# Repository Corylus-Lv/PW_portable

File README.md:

# PremierWave-EN Portable Board

過去に作った基板のEAGLE設計データを公開します。
LANTRONIX社のPremierWave-ENを使った応用基板ですが、リチウムイオン・バッテリーを使った移動機器に応用できるかもしれません。

**特に注意すべき事項：**  
リチウムイオン・バッテリーを使っているので、バッテリー容量に見合った充電電流を設定しないと、バッテリの破裂・炎上などの大きな事故につながる可能性がありますので、十分注意してください（LTC4055のデータシートを熟読する）

CC BY-NC-SA 3.0

**免責事項：**  
このプロジェクトに掲載した情報については「現状のまま」で、明示であるか暗黙であるかを問わず、何らの保証もありません。 
この情報の利用またはその他の扱いに関連した、請求、損害、その他の義務については一切の責任を負うものではありません。

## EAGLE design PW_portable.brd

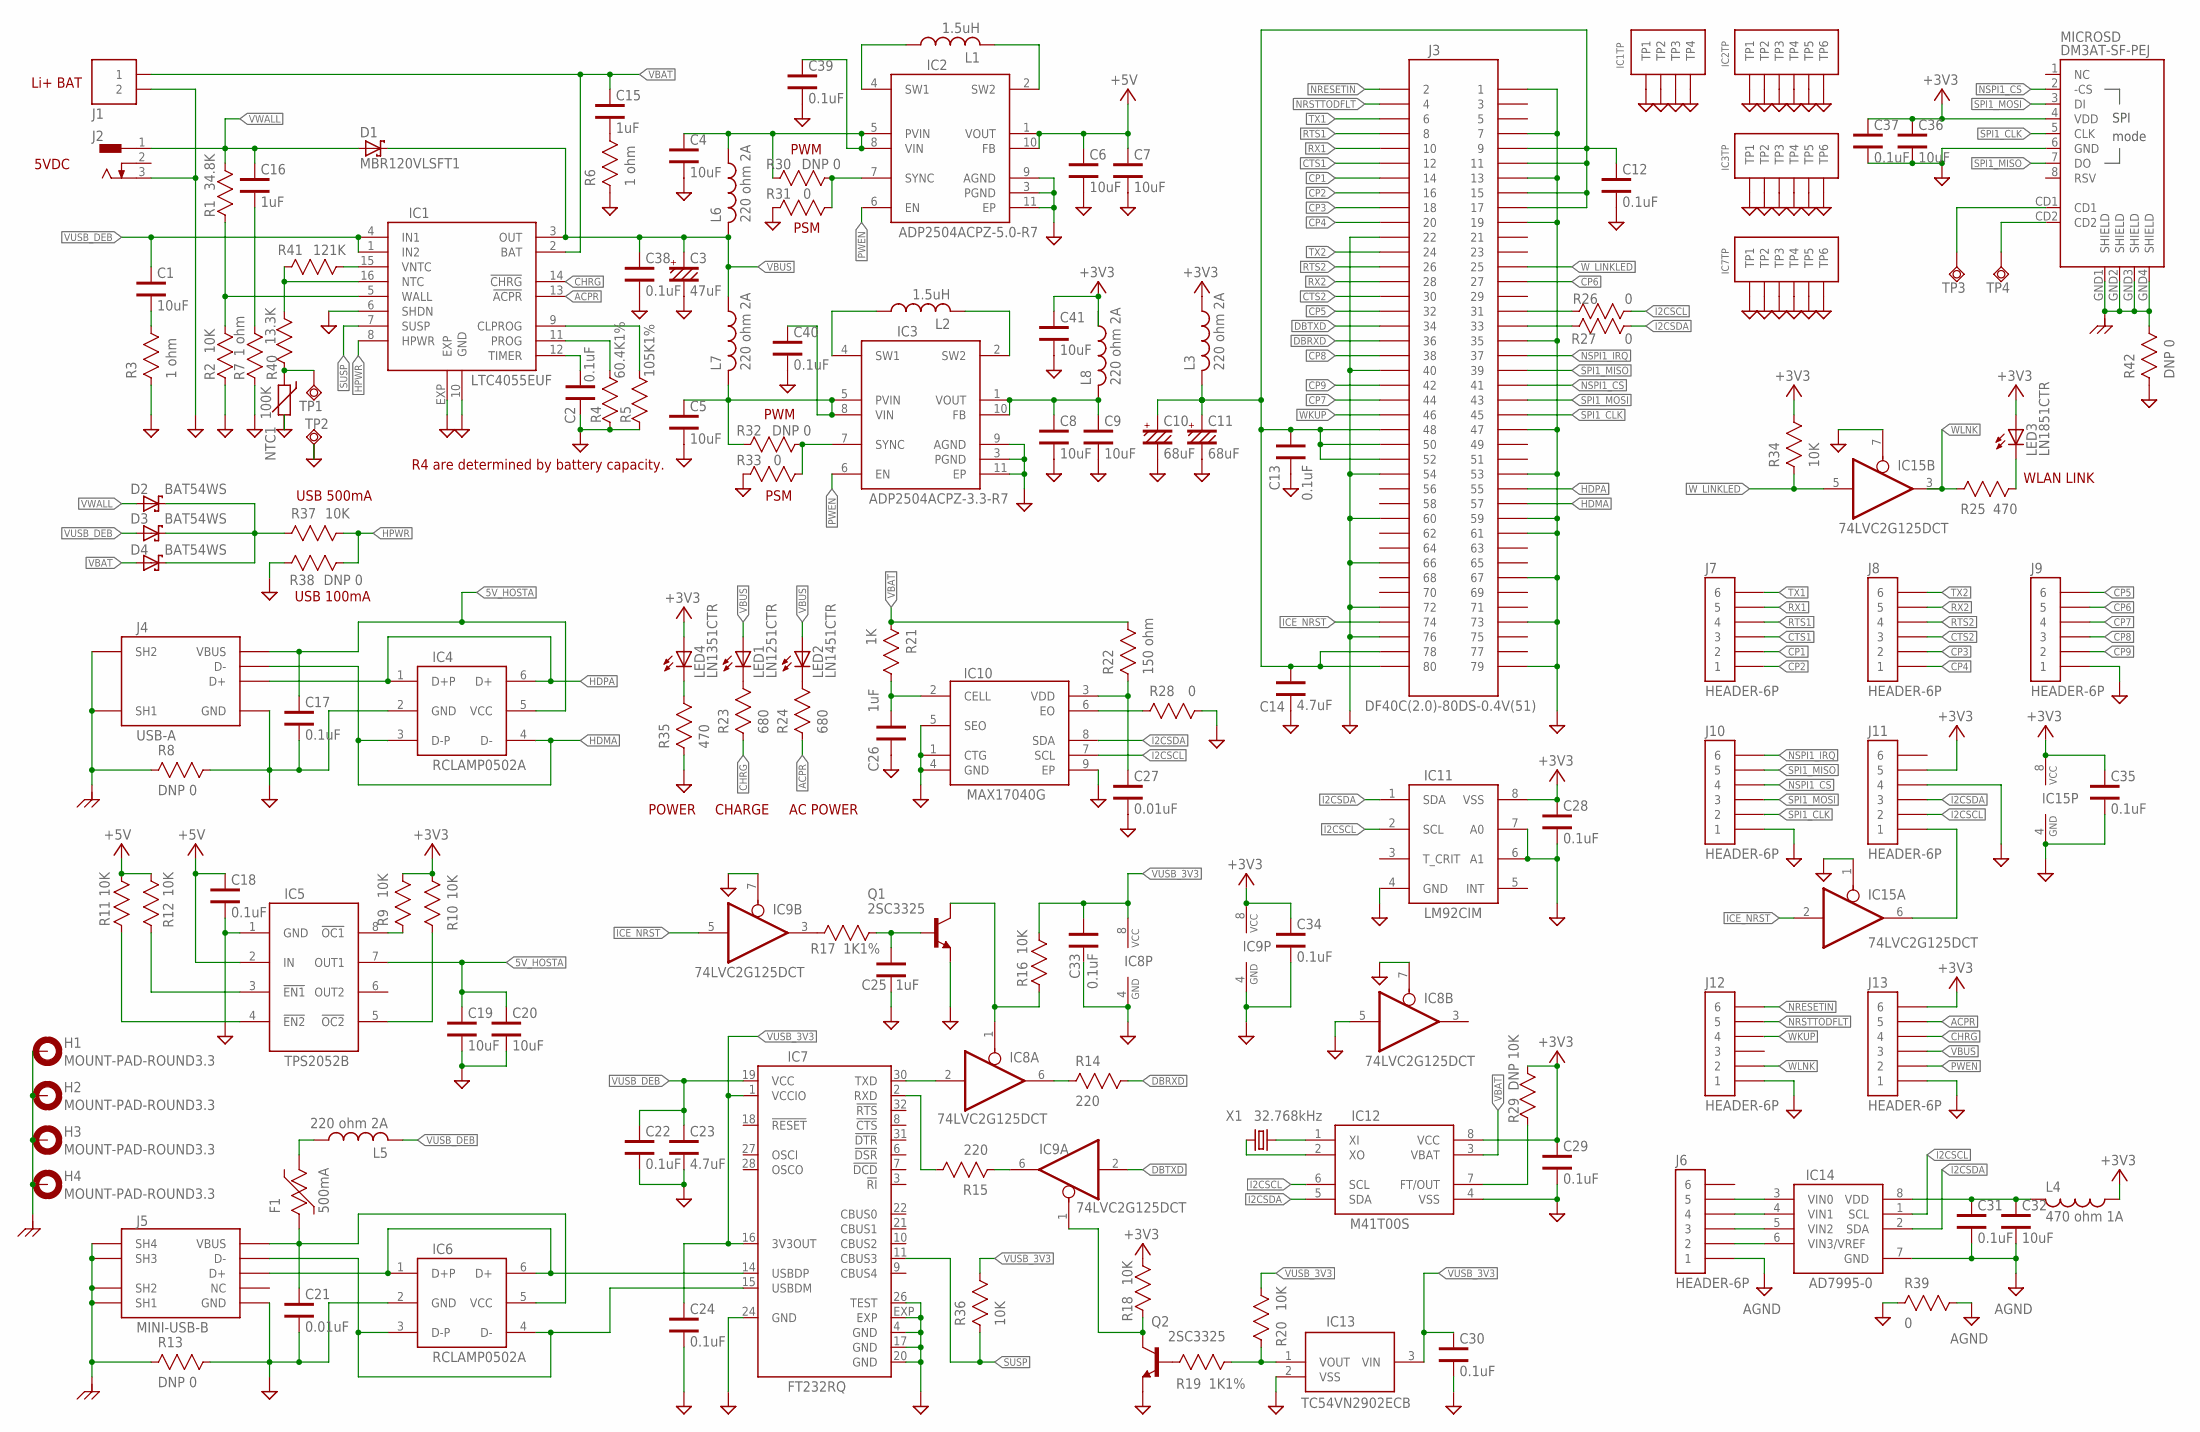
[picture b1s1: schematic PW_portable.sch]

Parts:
C1, C4, C5, C6, C7, C8, C9, C19, C20, C32, C36, C41: 10uF; C0603
C2, C12, C13, C17, C18, C22, C24, C28, C29, C30, C31, C33, C34, C35, C37, C38, C39, C40: 0.1uF; C0603
C3: 47uF; SMC_D
C10, C11: 68uF; SMC_D
C14, C23: 4.7uF; C0603
C15, C16, C25, C26: 1uF; C0603
C21, C27: 0.01uF; C0603
D1: MBR120VLSFT1; SOD123FL
D2, D3, D4: BAT54WS; SOD323
F1: 500mA; P1206
H1, H2, H3, H4: MOUNT-PAD-ROUND3.3; 3,3-PAD
IC1: LTC4055EUF; QFN16-4X4
IC2: ADP2504ACPZ-5.0-R7; LFCSP_WD-CP-10-9
IC3: ADP2504ACPZ-3.3-R7; LFCSP_WD-CP-10-9
IC4, IC6: RCLAMP0502A; SOT666
IC5: TPS2052B; D_R-PDSO-G08
IC7: FT232RQ; QFN32
IC8, IC9, IC15: 74LVC2G125DCT; SSOP08
IC10: MAX17040G; 8-TDFN
IC11: LM92CIM; SO08
IC12: M41T00S; SO08
IC13: TC54VN2902ECB; SOT23
IC14: AD7995-0; SOT23-8
J1: JACK-JST-2P-PW'SMD'; JST-SMD-2.0
J2: DCJ0202
J3: DF40C(2.0)-80DS-0.4V(51)
J4: USB-A
J5: MINI-USB-B; 1734035-2
J6, J7, J8, J9, J10, J11, J12, J13: HEADER-6P; 6P-2.54
L1, L2: 1.5uH; L1008
L3, L5, L6, L7, L8: 220 ohm 2A; L0603
L4: 470 ohm 1A; L0603
LED1: LN1251CTR; LED1208
LED2: LN1451CTR; LED1208
LED3: LN1851CTR; LED1208
LED4: LN1351CTR; LED1208
MICROSD: DM3AT-SF-PEJ
NTC1: 100K; R0603
Q1, Q2: 2SC3325; SOT23-BEC
R1: 34.8K; R0603
R2, R9, R10, R11, R12, R16, R18, R20, R34, R36, R37: 10K; R0603
R3, R6, R7: 1 ohm; R0603
R4: 60.4K1%; R0603
R5: 105K1%; R0603
R8, R13, R30, R32, R38, R42: DNP 0; R0603
R14, R15: 220; R0603
R17, R19: 1K1%; R0603
R21: 1K; R0603
R22: 150 ohm; R0603
R23, R24: 680; R0603
R25, R35: 470; R0603
R26, R27, R28, R31, R33, R39: 0; R0603
R29: DNP 10K; R0603
R40: 13.3K; R0603
R41: 121K; R0603
TP1, TP2, TP3, TP4: TPSQTP20SQ; TP20SQ
X1: 32.768kHz; FC255

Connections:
5V_HOSTA: C17.1, C19.1, C20.1, IC4.5 (VCC), IC5.7 (OUT1), J4.1 (VBUS)
+3V3: C28.1, C29.1, C34.1, C35.1, C36.1, C37.1, C41.1, IC9.8 (VCC), IC11.8 (VSS), IC12.8 (VCC), IC15.8 (VCC), J11.5, J13.6, L3.1, L4.1, L8.1, LED3.A, LED4.A, MICROSD.4 (VDD), R9.2, R10.2, R18.1, R29.2, R34.2
+5V: C6.1, C7.1, C18.1, IC2.1 (VOUT), IC2.10 (FB), IC5.2 (IN), R11.2, R12.2
ACPR: IC1.13 (!ACPR), J13.5, R24.1
AGND: C31.2, C32.2, IC14.7 (GND), J6.1, R39.2
CHRG: IC1.14 (!CHRG), J13.4, R23.1
CP1: J3.14, J7.2
CP2: J3.16, J7.1
CP3: J3.18, J8.2
CP4: J3.20, J8.1
CP5: J3.32, J9.6
CP6: J3.27, J9.5
CP7: J3.44, J9.4
CP8: J3.38, J9.3
CP9: J3.42, J9.2
CTS1: J3.12, J7.3
CTS2: J3.30, J8.3
DBRXD: J3.36, R14.2
DBTXD: IC9.2 (I), J3.34
DGND: C2.2, C3.-, C4.2, C5.2, C6.2, C7.2, C8.2, C9.2, C10.-, C11.-, C12.2, C13.2, C14.2, C17.2, C18.2, C19.2, C20.2, C21.2, C22.2, C23.2, C24.2, C25.2, C26.2, C27.2, C28.2, C29.2, C30.2, C33.2, C34.2, C35.2, C36.2, C37.2, C38.2, C39.2, C40.2, C41.2, IC1.6 (SHDN), IC1.10 (GND), IC1.EXP, IC1.P$1 (TP1), IC1.P$2 (TP2), IC1.P$3 (TP3), IC1.P$4 (TP4), IC2.3 (PGND), IC2.9 (AGND), IC2.11 (EP), IC2.P$1 (TP1), IC2.P$2 (TP2), IC2.P$3 (TP3), IC2.P$4 (TP4), IC2.P$5 (TP5), IC2.P$6 (TP6), IC3.3 (PGND), IC3.9 (AGND), IC3.11 (EP), IC3.P$1 (TP1), IC3.P$2 (TP2), IC3.P$3 (TP3), IC3.P$4 (TP4), IC3.P$5 (TP5), IC3.P$6 (TP6), IC4.2 (GND), IC5.1 (GND), IC6.2 (GND), IC7.4 (GND), IC7.17 (GND), IC7.20 (GND), IC7.24 (GND), IC7.26 (TEST), IC7.EXP, IC7.P$1 (TP1), IC7.P$2 (TP2), IC7.P$3 (TP3), IC7.P$4 (TP4), IC7.P$5 (TP5), IC7.P$6 (TP6), IC8.4 (GND), IC8.5 (I), IC8.7 (OE), IC9.4 (GND), IC9.7 (OE), IC10.1 (CTG), IC10.4 (GND), IC10.5 (SEO), IC10.9 (EP), IC11.4 (GND), IC11.6 (A1), IC11.7 (A0), IC12.4 (VSS), IC13.2 (VSS), IC15.1 (OE), IC15.4 (GND), IC15.7 (OE), J1.2, J2.3, J3.1, J3.7, J3.13, J3.19, J3.22, J3.35, J3.40, J3.47, J3.53, J3.54, J3.59, J3.60, J3.61, J3.66, J3.67, J3.72, J3.73, J3.76, J3.79, J4.4 (GND), J5.5 (GND), J9.1, J10.1, J11.4, J12.1, J13.1, MICROSD.6 (GND), NTC1.2, Q1.E, Q2.E, R2.1, R3.1, R4.1, R5.1, R6.1, R7.1, R8.2, R13.2, R28.2, R31.1, R33.1, R35.1, R38.1, R39.1, R42.1, TP2.TP
EGND: H1.B3,3, H2.B3,3, H3.B3,3, H4.B3,3, J4.5 (SH1), J4.6 (SH2), J5.M1 (SH1), J5.M2 (SH2), J5.M3 (SH3), J5.M4 (SH4), MICROSD.GND1 (SHIELD), MICROSD.GND2 (SHIELD), MICROSD.GND3 (SHIELD), MICROSD.GND4 (SHIELD), R8.1, R13.1, R42.2
HDMA: IC4.3 (D-P), IC4.4 (D-), J3.57, J4.2 (D-)
HDPA: IC4.1 (D+P), IC4.6 (D+), J3.55, J4.3 (D+)
HPWR: IC1.8 (HPWR), R37.2, R38.2
I2CSCL: IC10.7 (SCL), IC11.2 (SCL), IC12.6 (SCL), IC14.1 (SCL), J11.2, R26.2
I2CSDA: IC10.8 (SDA), IC11.1 (SDA), IC12.5 (SDA), IC14.2 (SDA), J11.3, R27.2
ICE_NRST: IC9.5 (I), IC15.2 (I), J3.74
unnamed: NTC1.1, R40.1, TP1.TP
unnamed: C26.1, IC10.2 (CELL), R21.2
unnamed: C2.1, IC1.12 (TIMER)
unnamed: C27.1, IC10.3 (VDD), R22.1
unnamed: IC1.5 (WALL), R1.1, R2.2
unnamed: C1.2, R3.2
unnamed: IC1.11 (PROG), R4.2
unnamed: IC1.9 (CLPROG), R5.2
unnamed: IC2.4 (SW1), L1.1
unnamed: IC2.2 (SW2), L1.2
unnamed: IC3.4 (SW1), L2.1
unnamed: IC3.2 (SW2), L2.2
unnamed: C10.+, C11.+, C12.1, C13.1, C14.1, J3.9, J3.11, J3.15, J3.17, J3.48, J3.50, J3.52, J3.78, J3.80, L3.2
unnamed: C16.2, R7.2
unnamed: IC5.3 (!EN1), R12.1
unnamed: IC5.8 (!OC1), R9.1
unnamed: IC5.5 (!OC2), R10.1
unnamed: C15.2, R6.2
unnamed: IC5.4 (!EN2), R11.1
unnamed: IC8.1 (OE), Q1.C, R16.1
unnamed: IC6.1 (D+P), IC6.6 (D+), IC7.14 (USBDP), J5.3 (D+)
unnamed: C21.1, F1.1, IC6.5 (VCC), J5.1 (VBUS)
unnamed: IC6.3 (D-P), IC6.4 (D-), IC7.15 (USBDM), J5.2 (D-)
unnamed: C25.1, Q1.B, R17.1
unnamed: IC9.1 (OE), Q2.C, R18.2
unnamed: Q2.B, R19.1
unnamed: IC7.30 (TXD), IC8.2 (I)
unnamed: IC7.2 (RXD), R15.2
unnamed: IC9.6 (O), R15.1
unnamed: IC8.6 (O), R14.1
unnamed: IC13.1 (VOUT), R19.2, R20.1
unnamed: IC10.6 (EO), R28.1
unnamed: IC9.3 (O), R17.2
unnamed: C31.1, C32.1, IC14.8 (VDD), L4.2
unnamed: IC12.2 (XO), X1.1
unnamed: LED1.C, R23.2
unnamed: LED2.C, R24.2
unnamed: IC14.6 (VIN3/VREF), J6.2
unnamed: IC14.5 (VIN2), J6.3
unnamed: IC14.4 (VIN1), J6.4
unnamed: IC14.3 (VIN0), J6.5
unnamed: IC15.6 (O), J11.1
unnamed: LED3.C, R25.2
unnamed: MICROSD.CD1, TP3.TP
unnamed: IC12.1 (XI), X1.2
unnamed: IC12.7 (FT/OUT), R29.1
unnamed: J3.31, R26.1
unnamed: J3.33, R27.1
unnamed: IC2.7 (SYNC), R30.2, R31.2
unnamed: IC3.7 (SYNC), R32.2, R33.2
unnamed: MICROSD.CD2, TP4.TP
unnamed: LED4.C, R35.2
unnamed: F1.2, L5.1
unnamed: C5.1, C40.1, IC3.5 (PVIN), IC3.8 (VIN), L7.2, R32.1
unnamed: C4.1, C39.1, IC2.5 (PVIN), IC2.8 (VIN), L6.1, R30.1
unnamed: D2.C, D3.C, D4.C, R37.1
unnamed: IC1.15 (VNTC), R41.1
unnamed: IC1.16 (NTC), R40.2, R41.2
unnamed: C8.1, C9.1, IC3.1 (VOUT), IC3.10 (FB), L8.2
NRESETIN: J3.2, J12.6
NRSTTODFLT: J3.4, J12.5
NSPI1_CS: J3.41, J10.4, MICROSD.2 (-CS)
NSPI1_IRQ: J3.37, J10.6
PWEN: IC2.6 (EN), IC3.6 (EN), J13.2
RTS1: J3.8, J7.4
RTS2: J3.26, J8.4
RX1: J3.10, J7.5
RX2: J3.28, J8.5
SPI1_CLK: J3.45, J10.2, MICROSD.5 (CLK)
SPI1_MISO: J3.39, J10.5, MICROSD.7 (DO)
SPI1_MOSI: J3.43, J10.3, MICROSD.3 (DI)
SUSP: IC1.7 (SUSP), IC7.11 (CBUS3), R36.1
TX1: J3.6, J7.6
TX2: J3.24, J8.6
VBAT: C15.1, D4.A, IC1.2 (BAT), IC12.3 (VBAT), J1.1, R21.1, R22.2
VBUS: C3.+, C38.1, D1.C, IC1.3 (OUT), J13.3, L6.2, L7.1, LED1.A, LED2.A
VUSB_3V3: C24.1, C30.1, C33.1, IC7.1 (VCCIO), IC7.16 (3V3OUT), IC8.8 (VCC), IC13.3 (VIN), R16.2, R20.2, R36.2
VUSB_DEB: C1.1, C22.1, C23.1, D3.A, IC1.1 (IN2), IC1.4 (IN1), IC7.19 (VCC), L5.2
VWALL: C16.1, D1.A, D2.A, J2.1, R1.2
WKUP: J3.46, J12.4
WLNK: IC15.3 (O), J12.2, R25.1
W_LINKLED: IC15.5 (I), J3.25, R34.1

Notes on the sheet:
Li+ BAT
5VDC
POWER
CHARGE
AC POWER
WLAN LINK
USB 500mA
USB 100mA
PWM
PSM
R4 are determined by battery capacity.

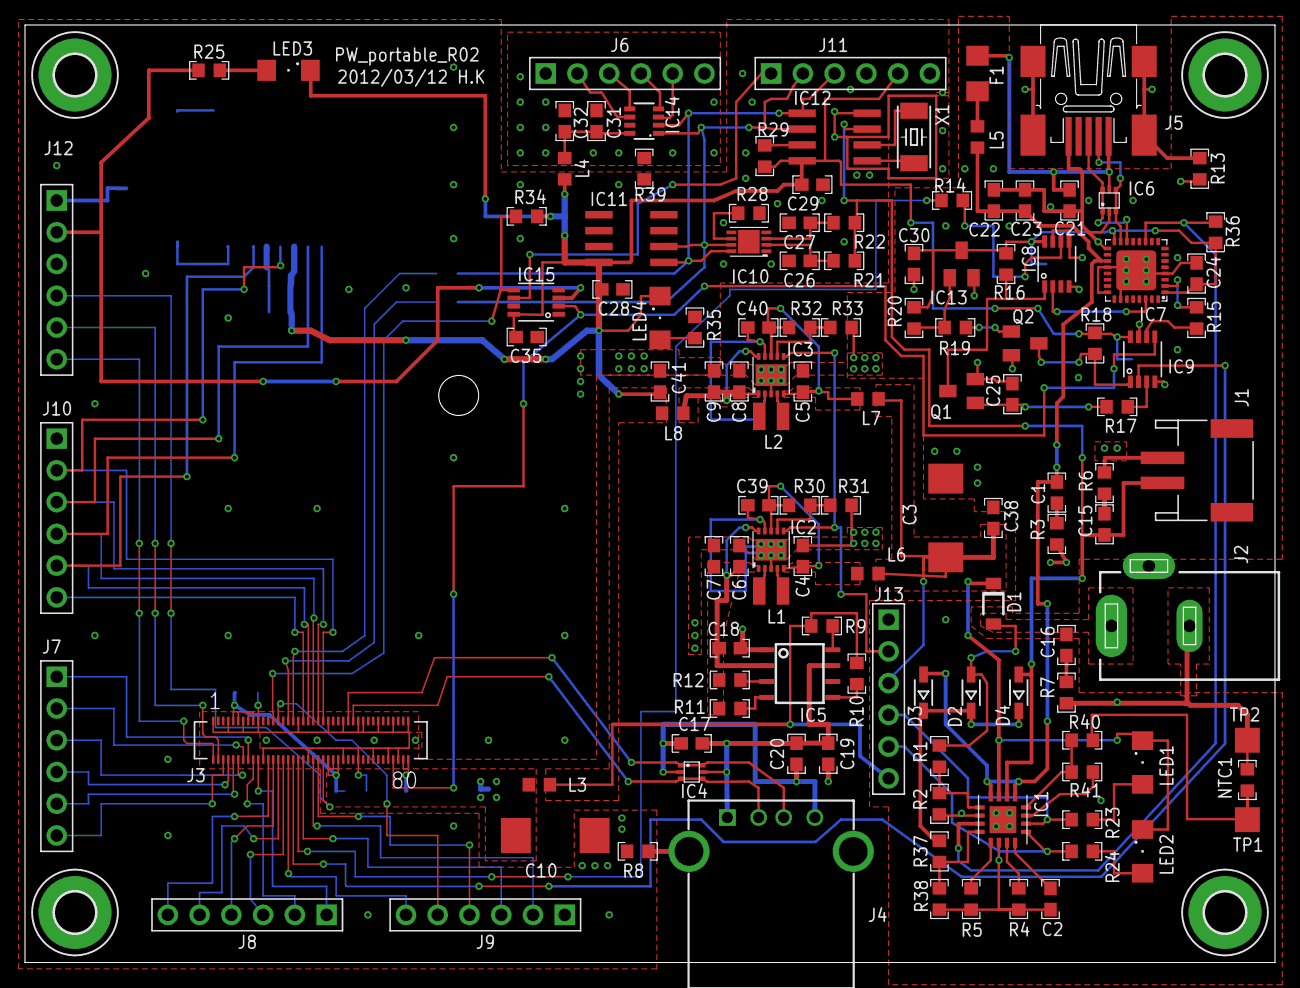
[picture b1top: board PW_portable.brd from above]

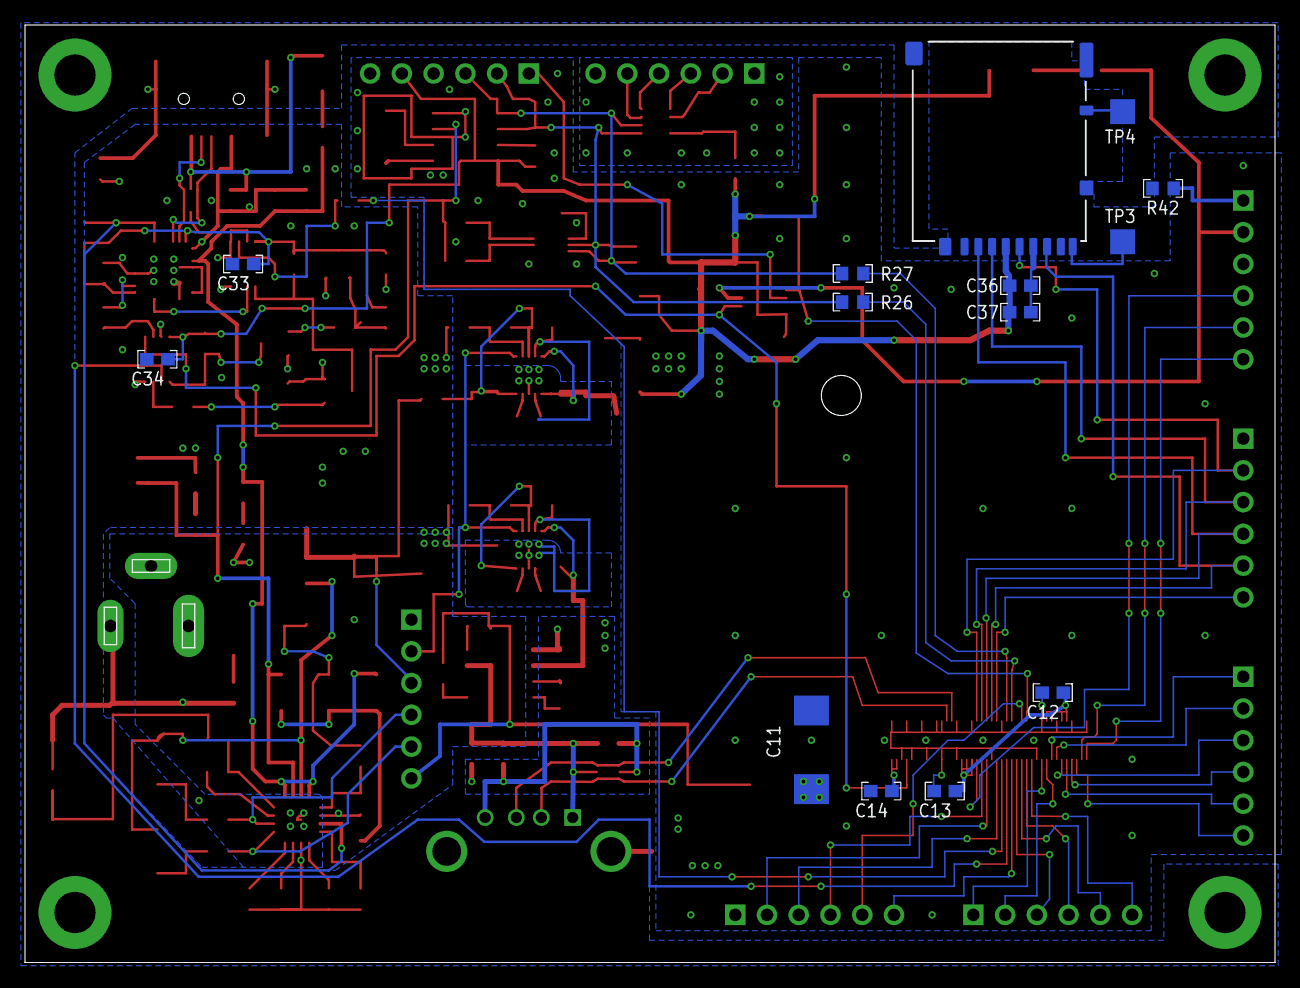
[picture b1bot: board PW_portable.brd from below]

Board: 2 copper layers, 100.0 x 75.0 mm, 141 parts (14 on the bottom side), 109 nets.
